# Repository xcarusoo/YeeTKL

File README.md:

# YeeTKL
Opensource TKL mechanical keyboard with RGB
epicly

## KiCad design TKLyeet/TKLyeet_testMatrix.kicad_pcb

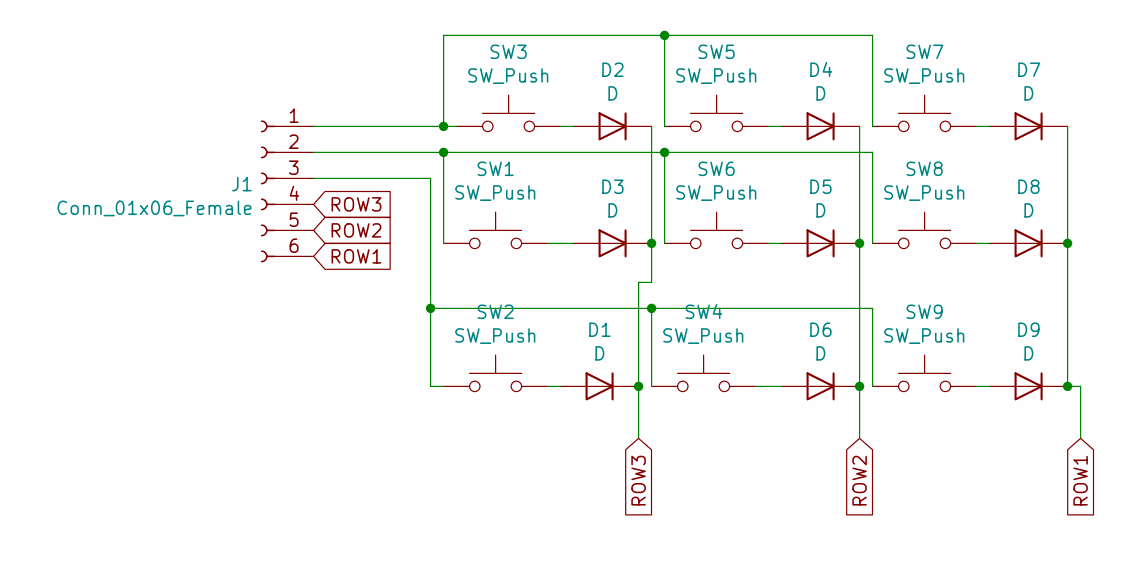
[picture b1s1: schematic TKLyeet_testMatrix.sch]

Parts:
D1, D2, D3, D4, D5, D6, D7, D8, D9: D; D_MiniMELF_Handsoldering
J1: Conn_01x06_Female; PinHeader_1x06_P2.54mm_Vertical
SW1, SW2, SW3, SW4, SW5, SW6, SW7, SW8, SW9: SW_Push; SW_Cherry_MX_1.00u_Plate

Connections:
unnamed: D1.2 (A), SW2.2
unnamed: D2.2 (A), SW3.2
unnamed: D3.2 (A), SW1.2
unnamed: D4.2 (A), SW5.2
unnamed: D5.2 (A), SW6.2
unnamed: D6.2 (A), SW4.2
unnamed: D7.2 (A), SW7.2
unnamed: D8.2 (A), SW8.2
unnamed: D9.2 (A), SW9.2
unnamed: J1.1, SW3.1, SW5.1, SW7.1
unnamed: J1.2, SW1.1, SW6.1, SW8.1
unnamed: J1.3, SW2.1, SW4.1, SW9.1
ROW1: D7.1 (K), D8.1 (K), D9.1 (K), J1.6
ROW2: D4.1 (K), D5.1 (K), D6.1 (K), J1.5
ROW3: D1.1 (K), D2.1 (K), D3.1 (K), J1.4

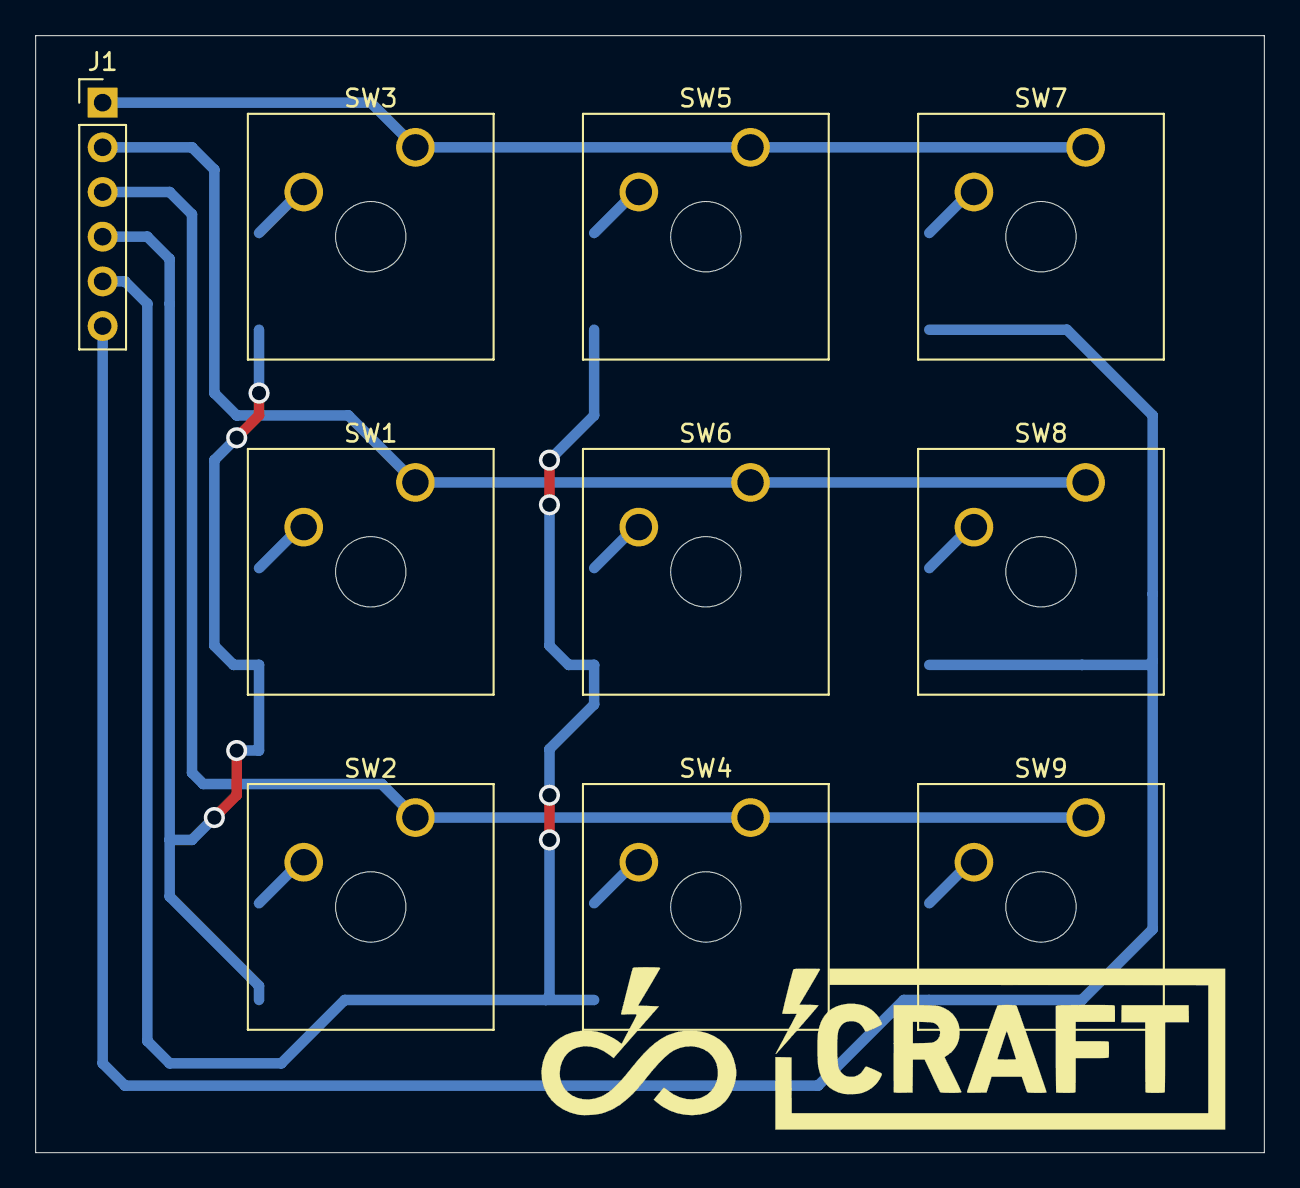
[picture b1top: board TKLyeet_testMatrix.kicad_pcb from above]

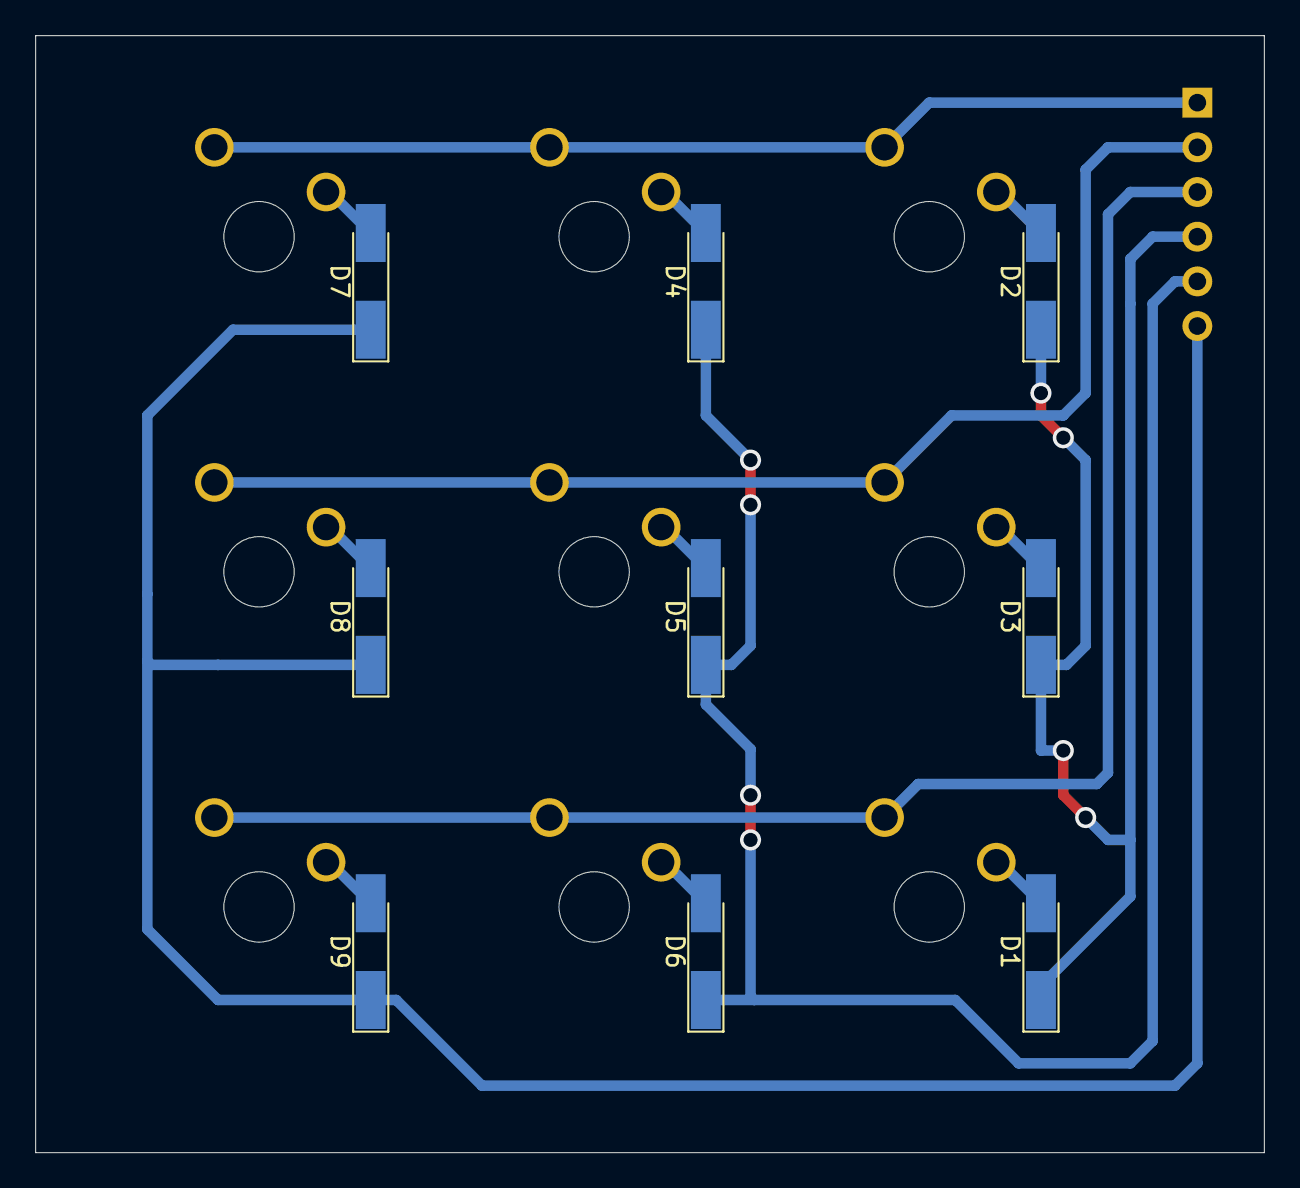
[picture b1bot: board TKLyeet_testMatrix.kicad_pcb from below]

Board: 2 copper layers, 69.9 x 63.5 mm, 19 parts (9 on the bottom side), 15 nets.

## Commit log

2019-10-21 pre v0
    [+] led switch symbol
    [+] cherry + apa 102 1u footprint
    [+] started work on stm32f103 basic circuit
2019-10-25 keypad 3x3
    zivijo Uros
2019-10-27 oops
